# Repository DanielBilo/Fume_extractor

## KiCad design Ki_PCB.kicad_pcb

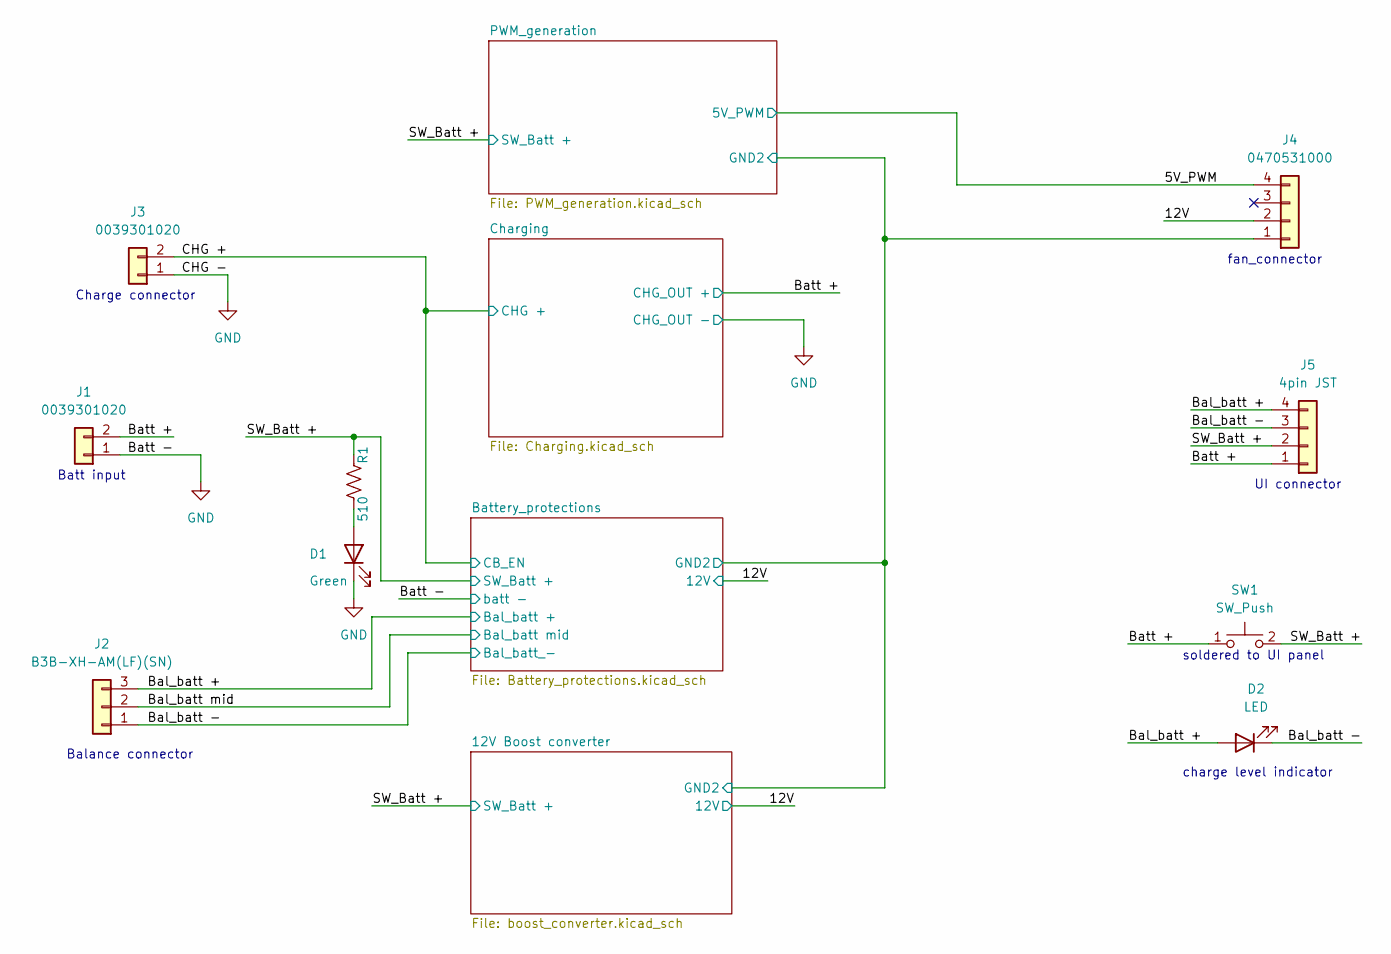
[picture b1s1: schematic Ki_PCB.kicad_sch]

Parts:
D1: Green; LED_D3.0mm
D2: LED; LED_D3.0mm
J1, J3: 0039301020; Molex_Mini-Fit_Jr_5569-02A2_2x01_P4.20mm_Horizontal; Part number 0039301020
J2: B3B-XH-AM(LF)(SN); JST_EH_B3B-EH-A_1x03_P2.50mm_Vertical; Part number B3B-XH-AM(LF)(SN)
J4: 0470531000; FanPinHeader_1x04_P2.54mm_Vertical; Part number 0470531000
J5: 4pin JST; JST_EH_B4B-EH-A_1x04_P2.50mm_Vertical
R1: 510; R_0805_2012Metric_Pad1.20x1.40mm_HandSolder
SW1: SW_Push; SW_Header_toggle_switch

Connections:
/5V_PWM: J4.4; also elsewhere on the board
/12V: J4.2; also elsewhere on the board
/12V Boost converter/GND2: J4.1; also elsewhere on the board
/Bal_batt +: D2.2 (A), J2.3, J5.4
/Bal_batt -: D2.1 (K), J2.1, J5.3; also elsewhere on the board
/Bal_batt mid: J2.2; also elsewhere on the board
/Batt +: J1.2, J5.1, SW1.1; also elsewhere on the board
/CHG +: J3.2; also elsewhere on the board
/SW_Batt +: J5.2, R1.2, SW1.2; also elsewhere on the board
GND: D1.1 (K), J1.1, J3.1; also elsewhere on the board
unnamed: D1.2 (A), R1.1

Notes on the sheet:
fan_connector
Batt input
Balance connector
Charge connector
UI connector
charge level indicator
soldered to UI panel

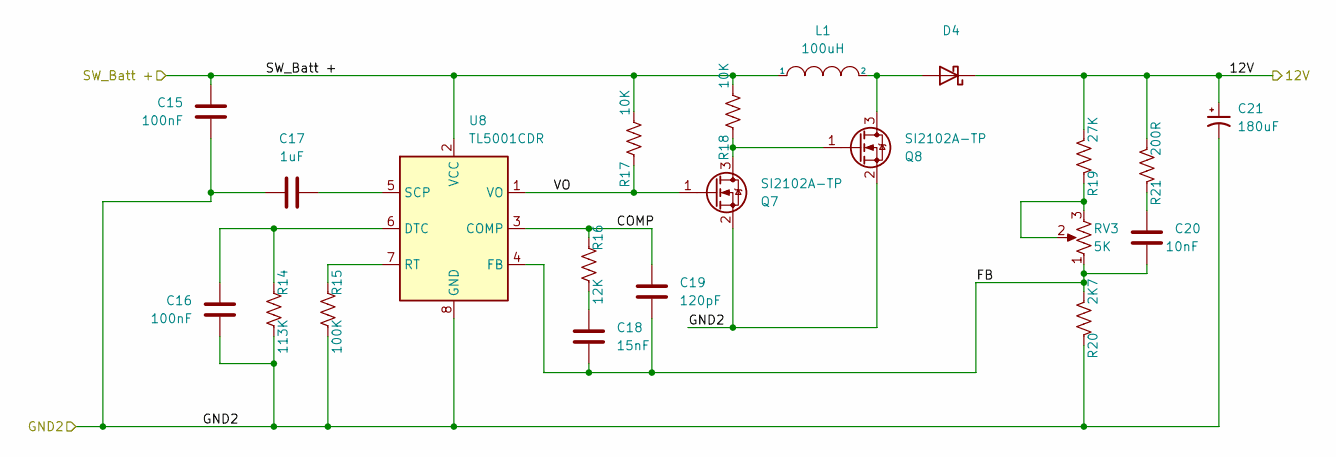
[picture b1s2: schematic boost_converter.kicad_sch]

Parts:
C15, C16: 100nF; C_0805_2012Metric_Pad1.18x1.45mm_HandSolder; Part number CML0805Y5V104ZT50V
C17: 1uF; C_0805_2012Metric_Pad1.18x1.45mm_HandSolder
C18: 15nF; C_0805_2012Metric_Pad1.18x1.45mm_HandSolder; Part number 885012207123
C19: 120pF; C_0805_2012Metric_Pad1.18x1.45mm_HandSolder
C20: 10nF; C_0805_2012Metric_Pad1.18x1.45mm_HandSolder
C21: 180uF; CP_Radial_D8.0mm_P3.50mm
D4: CRS05(TE85L,Q,M); Part number CRS05(TE85L,Q,M)
L1: 100uH; 74404063101; Part number 74404063101
Q7, Q8: SI2102A-TP; SOT-323_SC-70; Part number SI2102A-TP
R14: 113K; R_0805_2012Metric_Pad1.20x1.40mm_HandSolder; Part number RMCF0201FT113K
R15: 100K; R_0805_2012Metric_Pad1.20x1.40mm_HandSolder
R16: 12K; R_0805_2012Metric_Pad1.20x1.40mm_HandSolder
R17, R18: 10K; R_0805_2012Metric_Pad1.20x1.40mm_HandSolder; Part number RNCP0805FTD10K0
R19: 27K; R_0805_2012Metric_Pad1.20x1.40mm_HandSolder
R20: 2K7; R_0805_2012Metric_Pad1.20x1.40mm_HandSolder; Part number RMCF0805FT2K70
R21: 200R; R_0805_2012Metric_Pad1.20x1.40mm_HandSolder
RV3: 5K; CT6EP502; Part number CT6EP502
U8: TL5001CDR; SOIC-8_3.9x4.9mm_P1.27mm; Part number LT5001CDR

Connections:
/12V: C21.1, D4.1 (K), R19.1, R21.1; also elsewhere on the board
/12V Boost converter/COMP: C19.2, R16.2, U8.3 (COMP)
/12V Boost converter/FB: C18.1, C19.1, C20.1, R20.1, RV3.1, U8.4 (FB)
/12V Boost converter/GND2: C15.1, C16.1, C17.2, C21.2, Q7.2 (S), Q8.2 (S), R14.1, R15.1, R20.2, U8.8 (GND); also elsewhere on the board
/12V Boost converter/VO: Q7.1 (G), R17.2, U8.1 (VO)
/SW_Batt +: C15.2, L1.1, R17.1, R18.1, U8.2 (VCC); also elsewhere on the board
unnamed: C16.2, R14.2, U8.6 (DTC)
unnamed: C17.1, U8.5 (SCP)
unnamed: C18.2, R16.1
unnamed: C20.2, R21.2
unnamed: D4.2 (A), L1.2, Q8.3 (D)
unnamed: Q7.3 (D), Q8.1 (G), R18.2
unnamed: R15.2, U8.7 (RT)
unnamed: R19.2, RV3.2, RV3.3

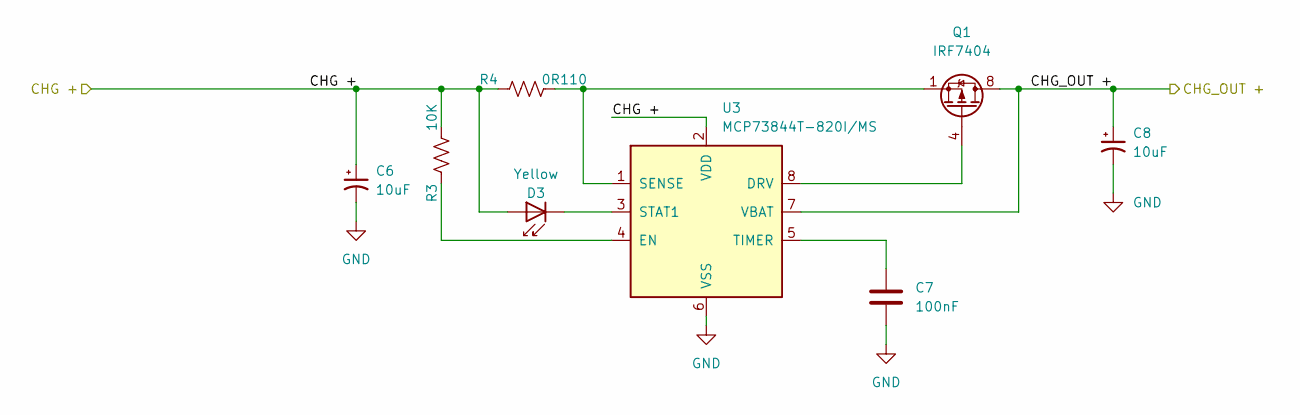
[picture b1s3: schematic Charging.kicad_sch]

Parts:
C6, C8: 10uF; C_0805_2012Metric_Pad1.18x1.45mm_HandSolder; Part number GRM21BR61H106KE43K
C7: 100nF; C_0805_2012Metric_Pad1.18x1.45mm_HandSolder; Part number CML0805Y5V104ZT50V
D3: Yellow; LED_D3.0mm
Q1: IRF7404; SOIC-8_3.9x4.9mm_P1.27mm
R3: 10K; R_0805_2012Metric_Pad1.20x1.40mm_HandSolder; Part number RNCP0805FTD10K0
R4: 0R110; R_0805_2012Metric_Pad1.20x1.40mm_HandSolder; Part number ERJ-6BSFR11V
U3: MCP73844T-820I/MS; MSOP-8_3x3mm_P0.65mm; Part number MCP73844T-820I/MS

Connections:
/Batt +: C8.1, Q1.5 (D), Q1.6 (D), Q1.7 (D), Q1.8 (D), U3.7 (VBAT); also elsewhere on the board
/CHG +: C6.1, D3.2 (A), R3.1, R4.2, U3.2 (VDD); also elsewhere on the board
GND: C6.2, C7.2, C8.2, U3.6 (VSS); also elsewhere on the board
unnamed: C7.1, U3.5 (TIMER)
unnamed: D3.1 (K), U3.3 (STAT1)
unnamed: R3.2, U3.4 (EN)
unnamed: Q1.1 (S), Q1.2 (S), Q1.3 (S), R4.1, U3.1 (SENSE)
unnamed: Q1.4 (G), U3.8 (DRV)

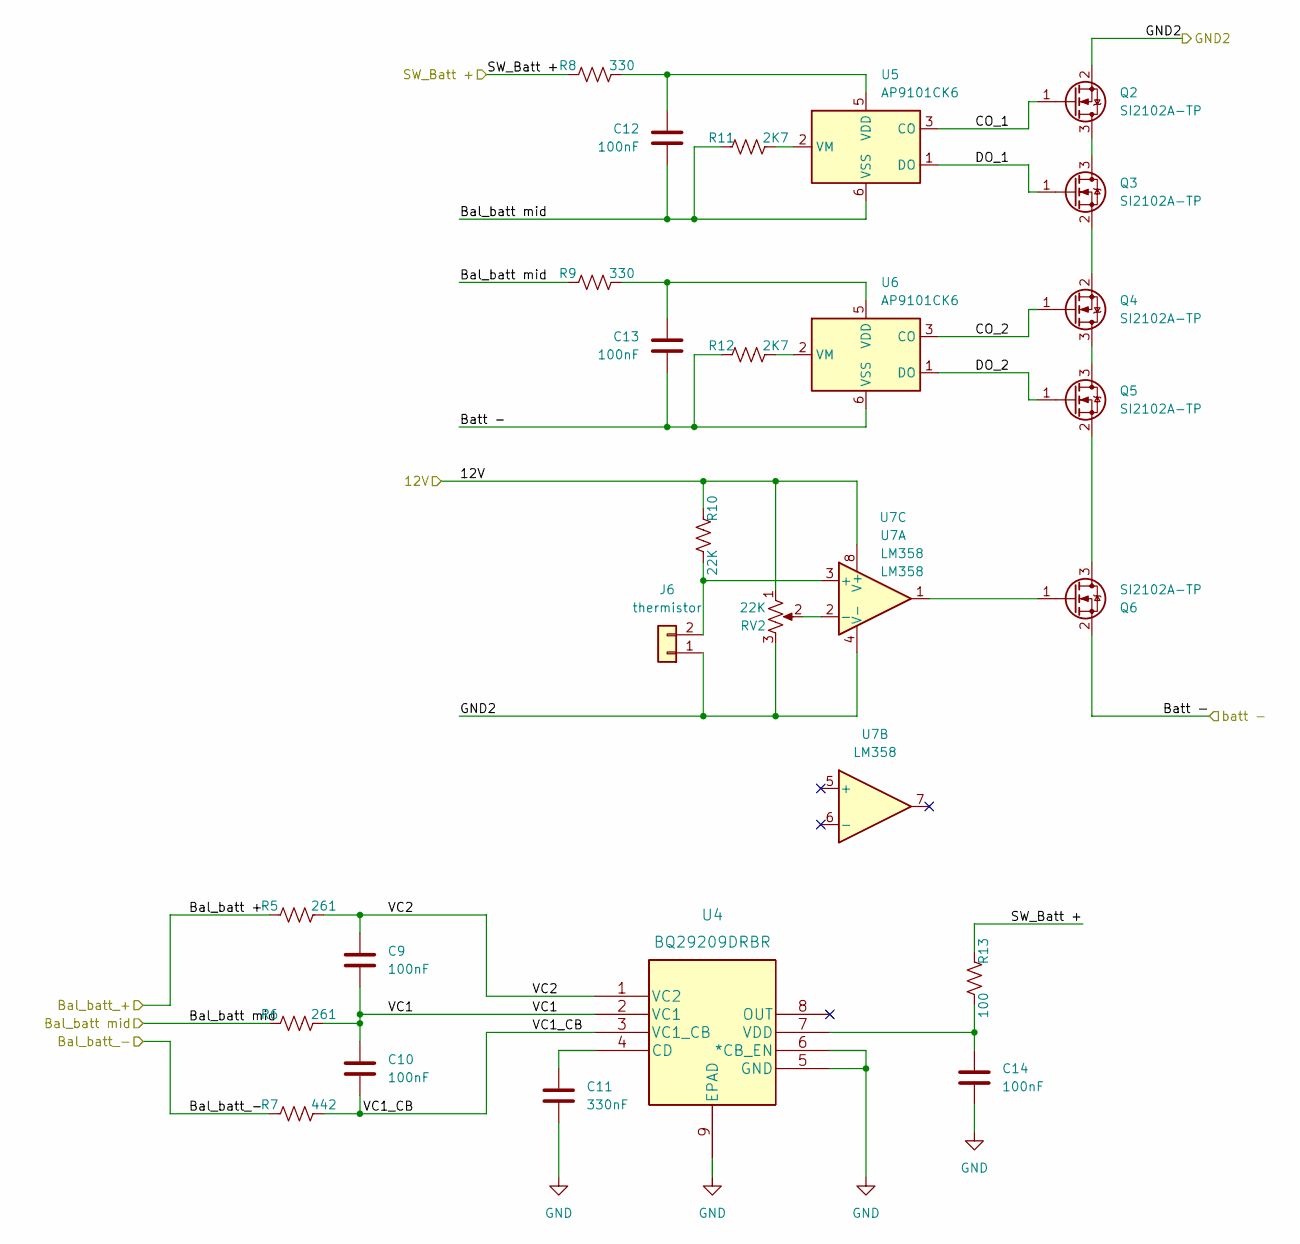
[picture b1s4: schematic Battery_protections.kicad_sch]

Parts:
C9, C10, C12, C13, C14: 100nF; C_0805_2012Metric_Pad1.18x1.45mm_HandSolder; Part number CML0805Y5V104ZT50V
C11: 330nF; C_0805_2012Metric_Pad1.18x1.45mm_HandSolder; Part number 885012207101
J6: thermistor; JST_EH_B2B-EH-A_1x02_P2.50mm_Vertical
Q2, Q3, Q4, Q5, Q6: SI2102A-TP; SOT-323_SC-70; Part number SI2102A-TP
R5, R6: 261; R_0805_2012Metric_Pad1.20x1.40mm_HandSolder; Part number RMCF0805FG261R
R7: 442; R_0805_2012Metric_Pad1.20x1.40mm_HandSolder; Part number RMCF0805FT442R
R8, R9: 330; R_0805_2012Metric_Pad1.20x1.40mm_HandSolder; Part number RMCF0805FT330R
R10: 22K; R_0805_2012Metric_Pad1.20x1.40mm_HandSolder; Part number RMCF0201FT113K
R11, R12: 2K7; R_0805_2012Metric_Pad1.20x1.40mm_HandSolder; Part number RMCF0805FT2K70
R13: 100; R_0805_2012Metric_Pad1.20x1.40mm_HandSolder; Part number RMCF0805FT100R
RV2: 22K; 3362P-1-223LF; Part number 3362P-1-223LF
U4: BQ29209DRBR; Part number BQ29209DRBR
U5, U6: AP9101CK6; SOT-23-6; Part number AP9101CK6
U7: LM358; DIP-8_W7.62mm_LongPads

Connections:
/12V: R10.2, RV2.1, U7.8 (V+); also elsewhere on the board
/12V Boost converter/GND2: J6.1, Q2.2 (S), RV2.3, U7.4 (V-); also elsewhere on the board
/Bal_batt -: R7.2; also elsewhere on the board
/Bal_batt mid: C12.1, R6.2, R9.2, R11.2, U5.6 (VSS); also elsewhere on the board
/Battery_protections/Bal_batt +: R5.2
/Battery_protections/CO_1: Q2.1 (G), U5.3 (CO)
/Battery_protections/CO_2: Q4.1 (G), U6.3 (CO)
/Battery_protections/DO_1: Q3.1 (G), U5.1 (DO)
/Battery_protections/DO_2: Q5.1 (G), U6.1 (DO)
/Battery_protections/VC1: C9.2, C10.1, R6.1, U4.2 (VC1)
/Battery_protections/VC1_CB: C10.2, R7.1, U4.3 (VC1_CB)
/Battery_protections/VC2: C9.1, R5.1, U4.1 (VC2)
/SW_Batt +: R8.2, R13.2; also elsewhere on the board
GND: C11.2, C13.1, C14.2, Q6.2 (S), R12.2, U4.5 (GND), U4.6 (*CB_EN), U4.9 (EPAD), U6.6 (VSS); also elsewhere on the board
unnamed: C11.1, U4.4 (CD)
unnamed: C12.2, R8.1, U5.5 (VDD)
unnamed: C13.2, R9.1, U6.5 (VDD)
unnamed: C14.1, R13.1, U4.7 (VDD)
unnamed: J6.2, R10.1, U7.3 (+)
unnamed: Q2.3 (D), Q3.3 (D)
unnamed: Q3.2 (S), Q4.2 (S)
unnamed: Q4.3 (D), Q5.3 (D)
unnamed: Q5.2 (S), Q6.3 (D)
unnamed: Q6.1 (G), U7.1
unnamed: R11.1, U5.2 (VM)
unnamed: R12.1, U6.2 (VM)
unnamed: RV2.2, U7.2 (-)

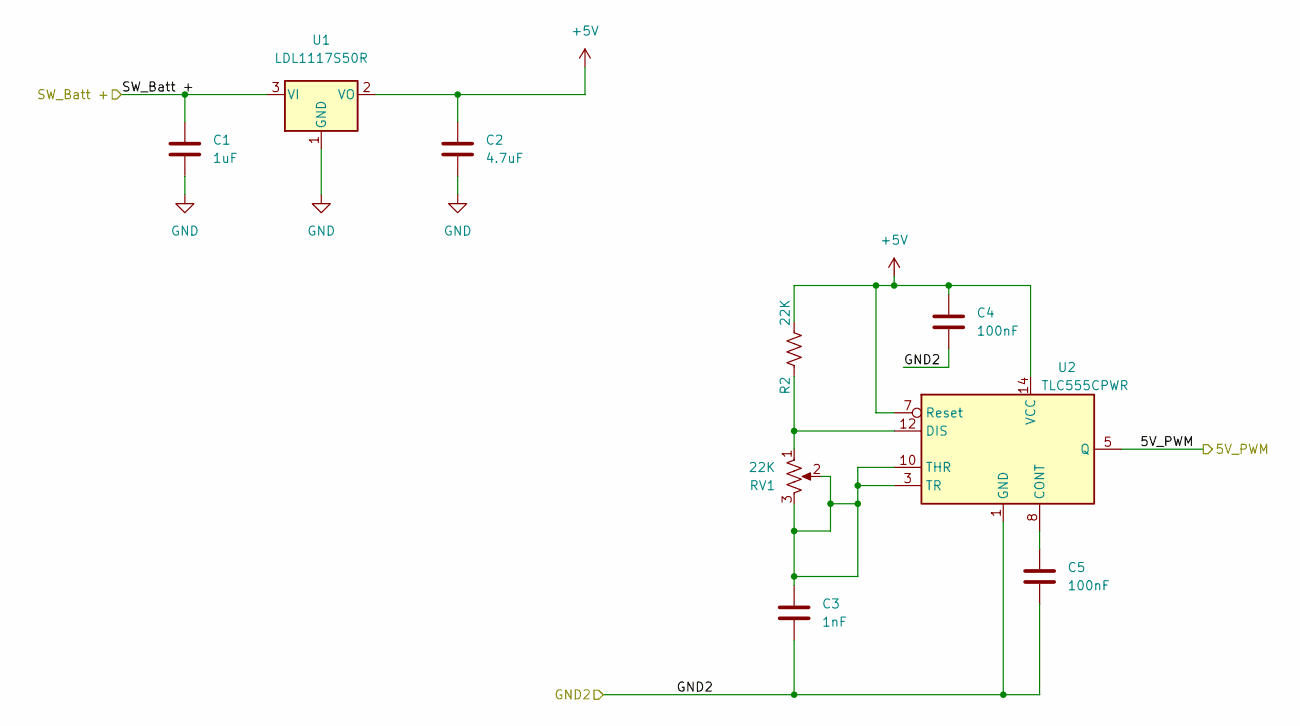
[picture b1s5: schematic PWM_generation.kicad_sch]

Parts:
C1: 1uF; C_0805_2012Metric_Pad1.18x1.45mm_HandSolder; Part number CL21B105KAFNNNE
C2: 4.7uF; C_0805_2012Metric_Pad1.18x1.45mm_HandSolder; Part number CL21A475KAQNNNG
C3: 1nF; C_0805_2012Metric_Pad1.18x1.45mm_HandSolder; Part number 08055C102KAT2A
C4, C5: 100nF; C_0805_2012Metric_Pad1.18x1.45mm_HandSolder; Part number CML0805Y5V104ZT50V
R2: 22K; R_0805_2012Metric_Pad1.20x1.40mm_HandSolder
RV1: 22K; PC16SH-10IP06-223A2020-TA; Part number PC16SH-10IP06-223A2020-TA
U1: LDL1117S50R; SOT-223-3_TabPin2; Part number LDL1117S50R
U2: TLC555CPWR; TSSOP-14_4.4x5mm_P0.65mm; Part number TLC555CPWR

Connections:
+5V: C2.1, C4.1, R2.1, U1.2 (VO), U2.7 (Reset), U2.14 (VCC)
/5V_PWM: U2.5 (Q); also elsewhere on the board
/12V Boost converter/GND2: C3.2, C4.2, C5.2, U2.1 (GND); also elsewhere on the board
/SW_Batt +: C1.1, U1.3 (VI); also elsewhere on the board
GND: C1.2, C2.2, U1.1 (GND); also elsewhere on the board
unnamed: C3.1, RV1.2, RV1.3, U2.3 (TR), U2.10 (THR)
unnamed: C5.1, U2.8 (CONT)
unnamed: R2.2, RV1.1, U2.12 (DIS)
unnamed: U2.2 (NC), U2.4 (NC), U2.6 (NC), U2.9 (NC), U2.11 (NC), U2.13 (NC)

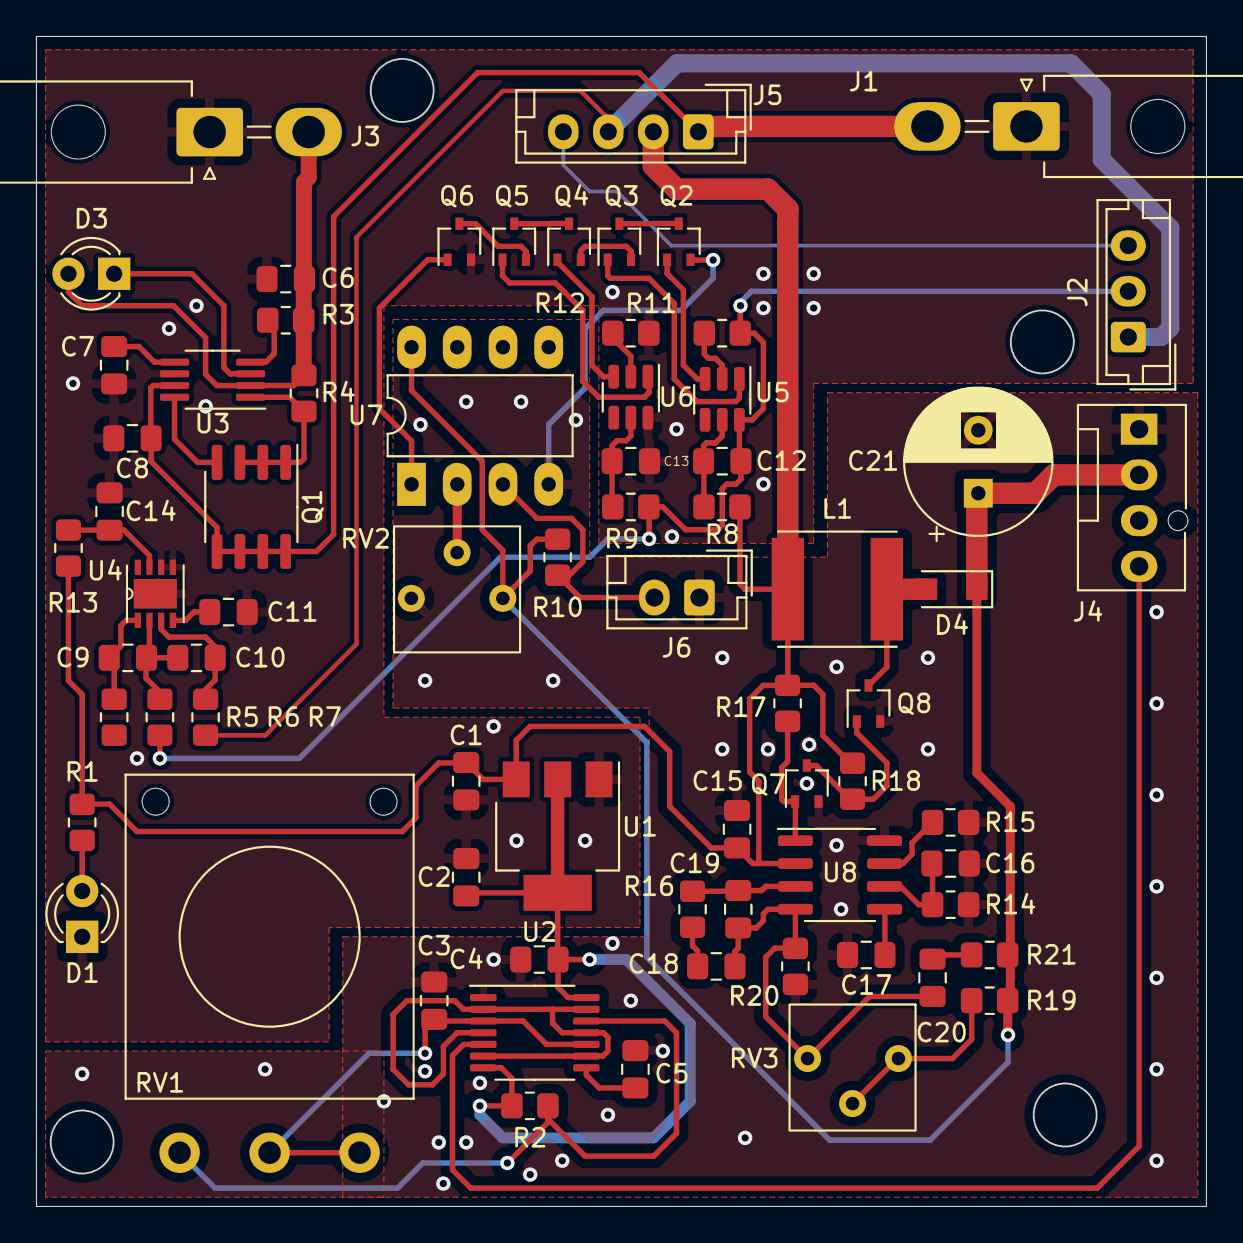
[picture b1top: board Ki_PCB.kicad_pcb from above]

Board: 2 copper layers, 65.0 x 64.9 mm, 71 parts (0 on the bottom side), 52 nets.

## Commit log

2022-12-31 Fixes brought on laptop
2022-12-31 Added new files (library footprint)
2023-02-27 Initial layout
2023-02-27 layout not routed
2023-02-28 Last commit from desktop
2023-03-01 First layout done
2023-05-10 Re took on project started routing
2023-05-10 Removed backup folder
2023-05-10 Added gitignore for backup file tracking
2023-05-11 layout 1 done, dsr errors with gnd plane clearances
2023-08-18 1st Gerber creatd Please enter the commit message for your changes. Lines starting
2023-08-18 added drill files
2023-08-18 added drill map
